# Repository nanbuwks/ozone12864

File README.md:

# OZONE12864

ESP32 ozone meater with LCD JLX12864G-332-BN

# sensor

SPEC electrochemical 3SP_O3_20 DIP 

# principle

Potentiostat method. see:
https://qiita.com/nanbuwks/items/b0f3cb8982ab1c29c718

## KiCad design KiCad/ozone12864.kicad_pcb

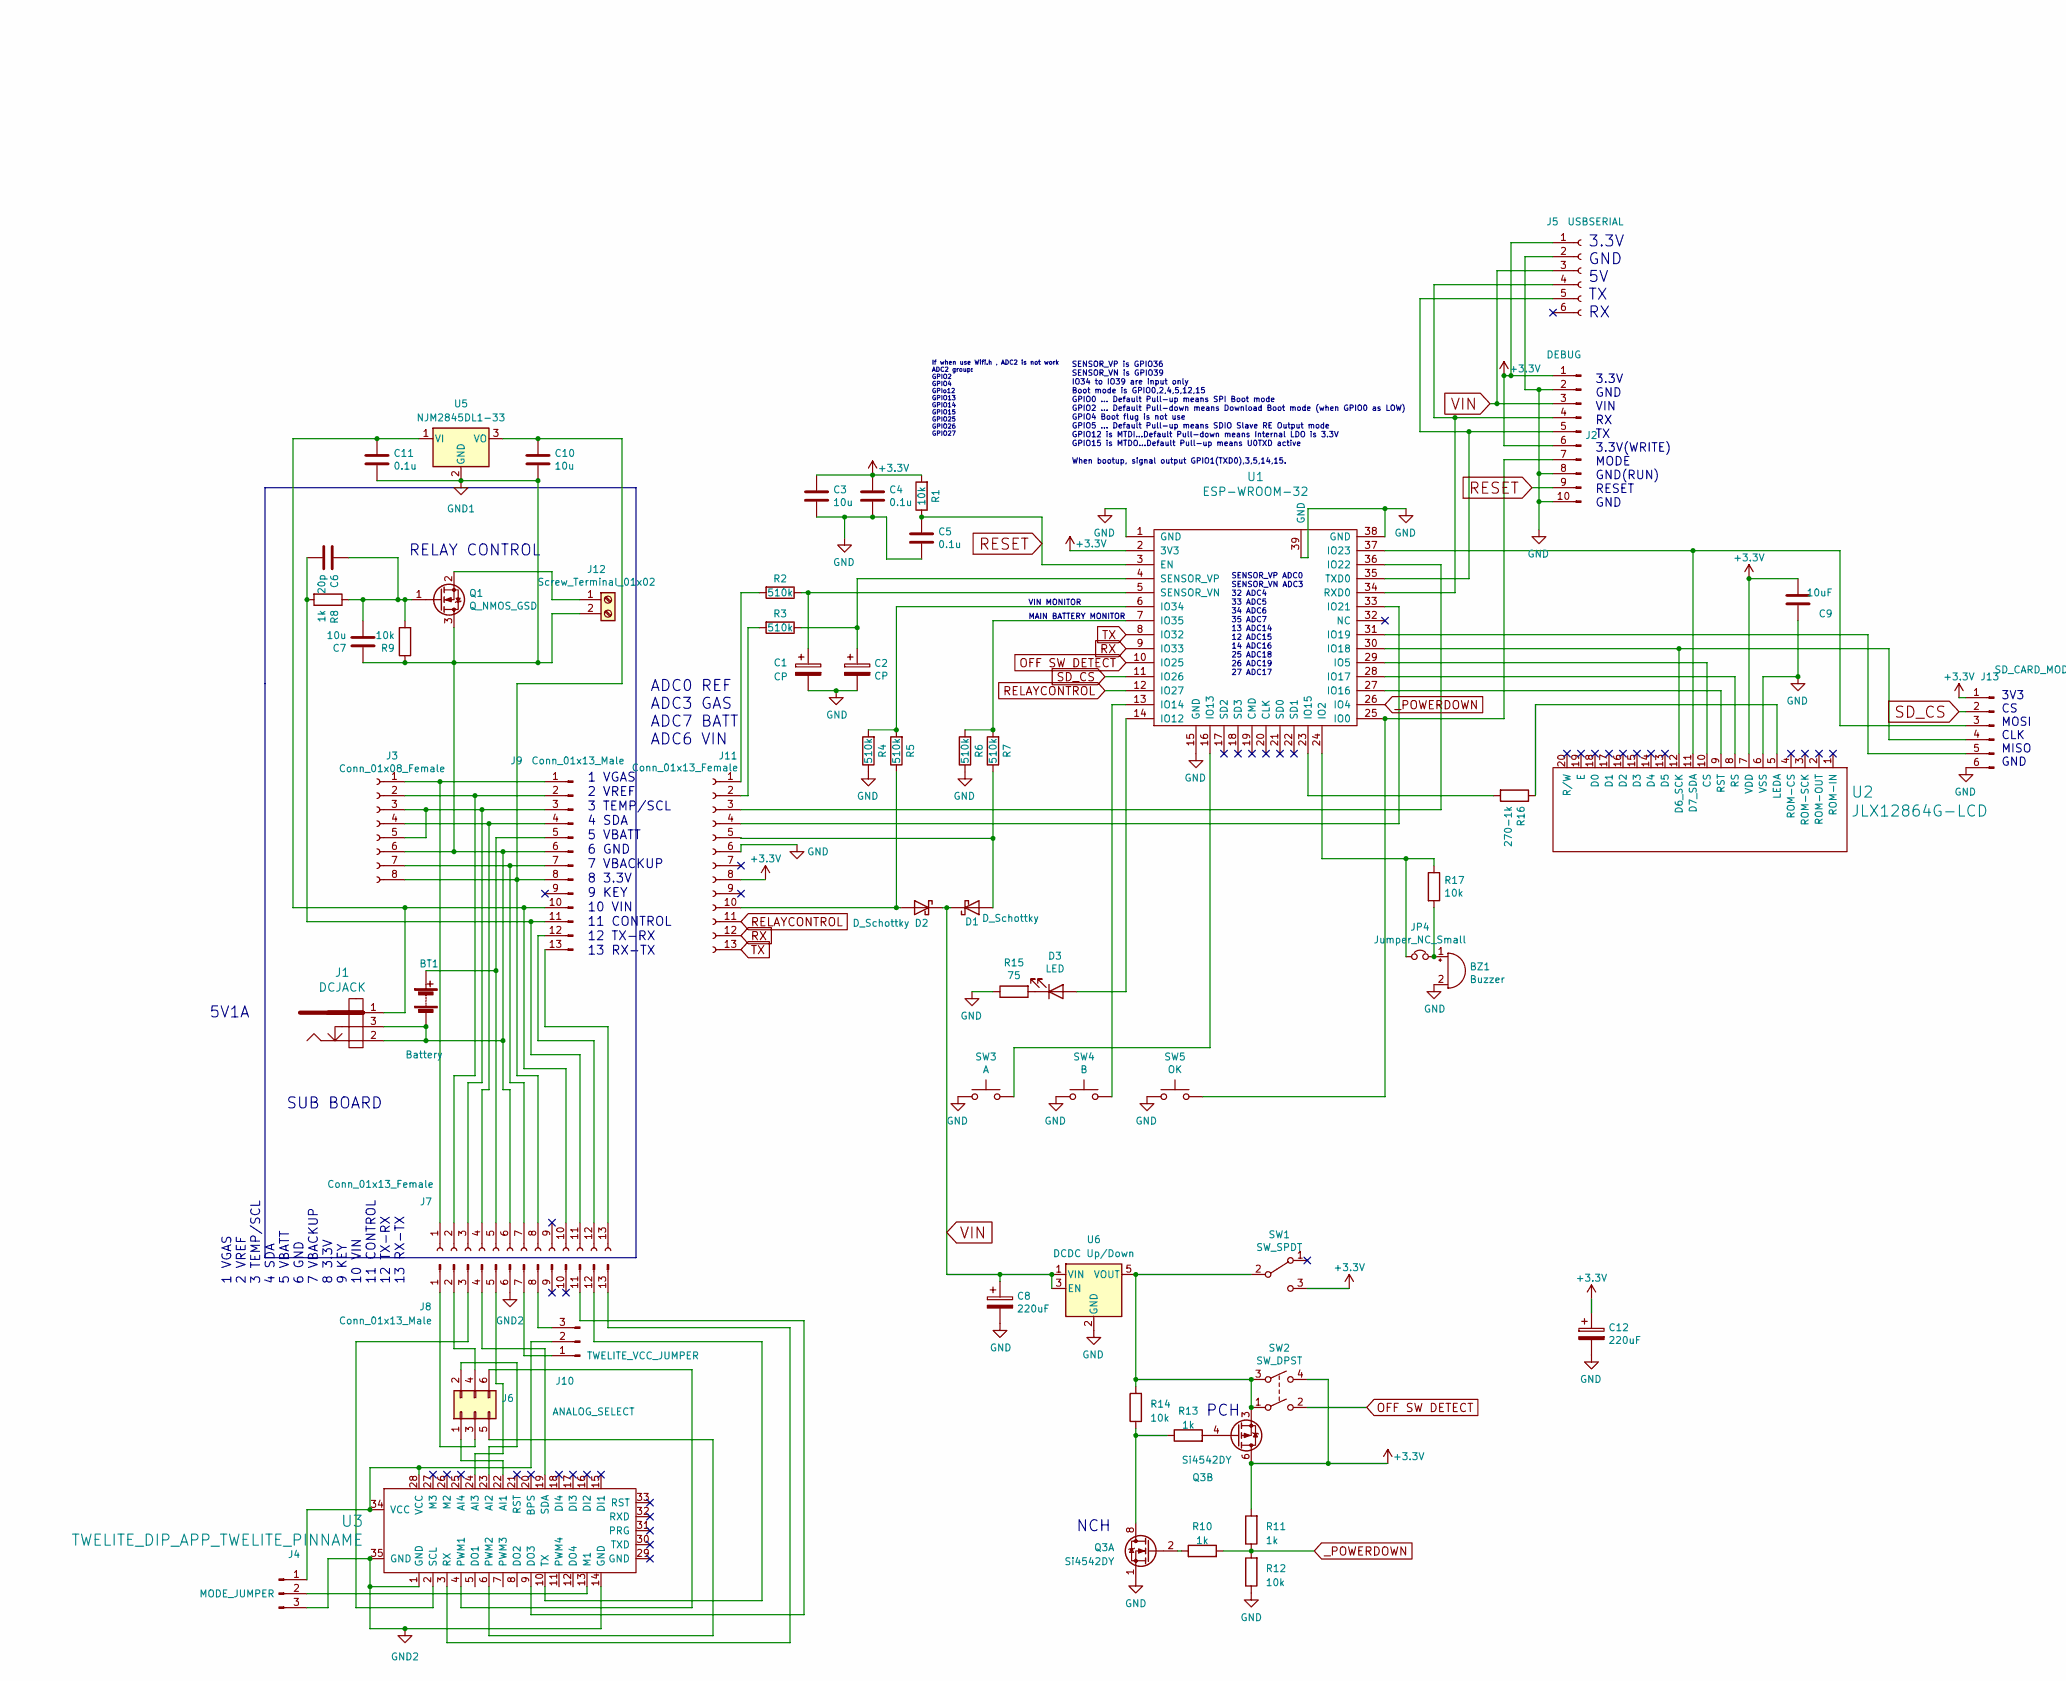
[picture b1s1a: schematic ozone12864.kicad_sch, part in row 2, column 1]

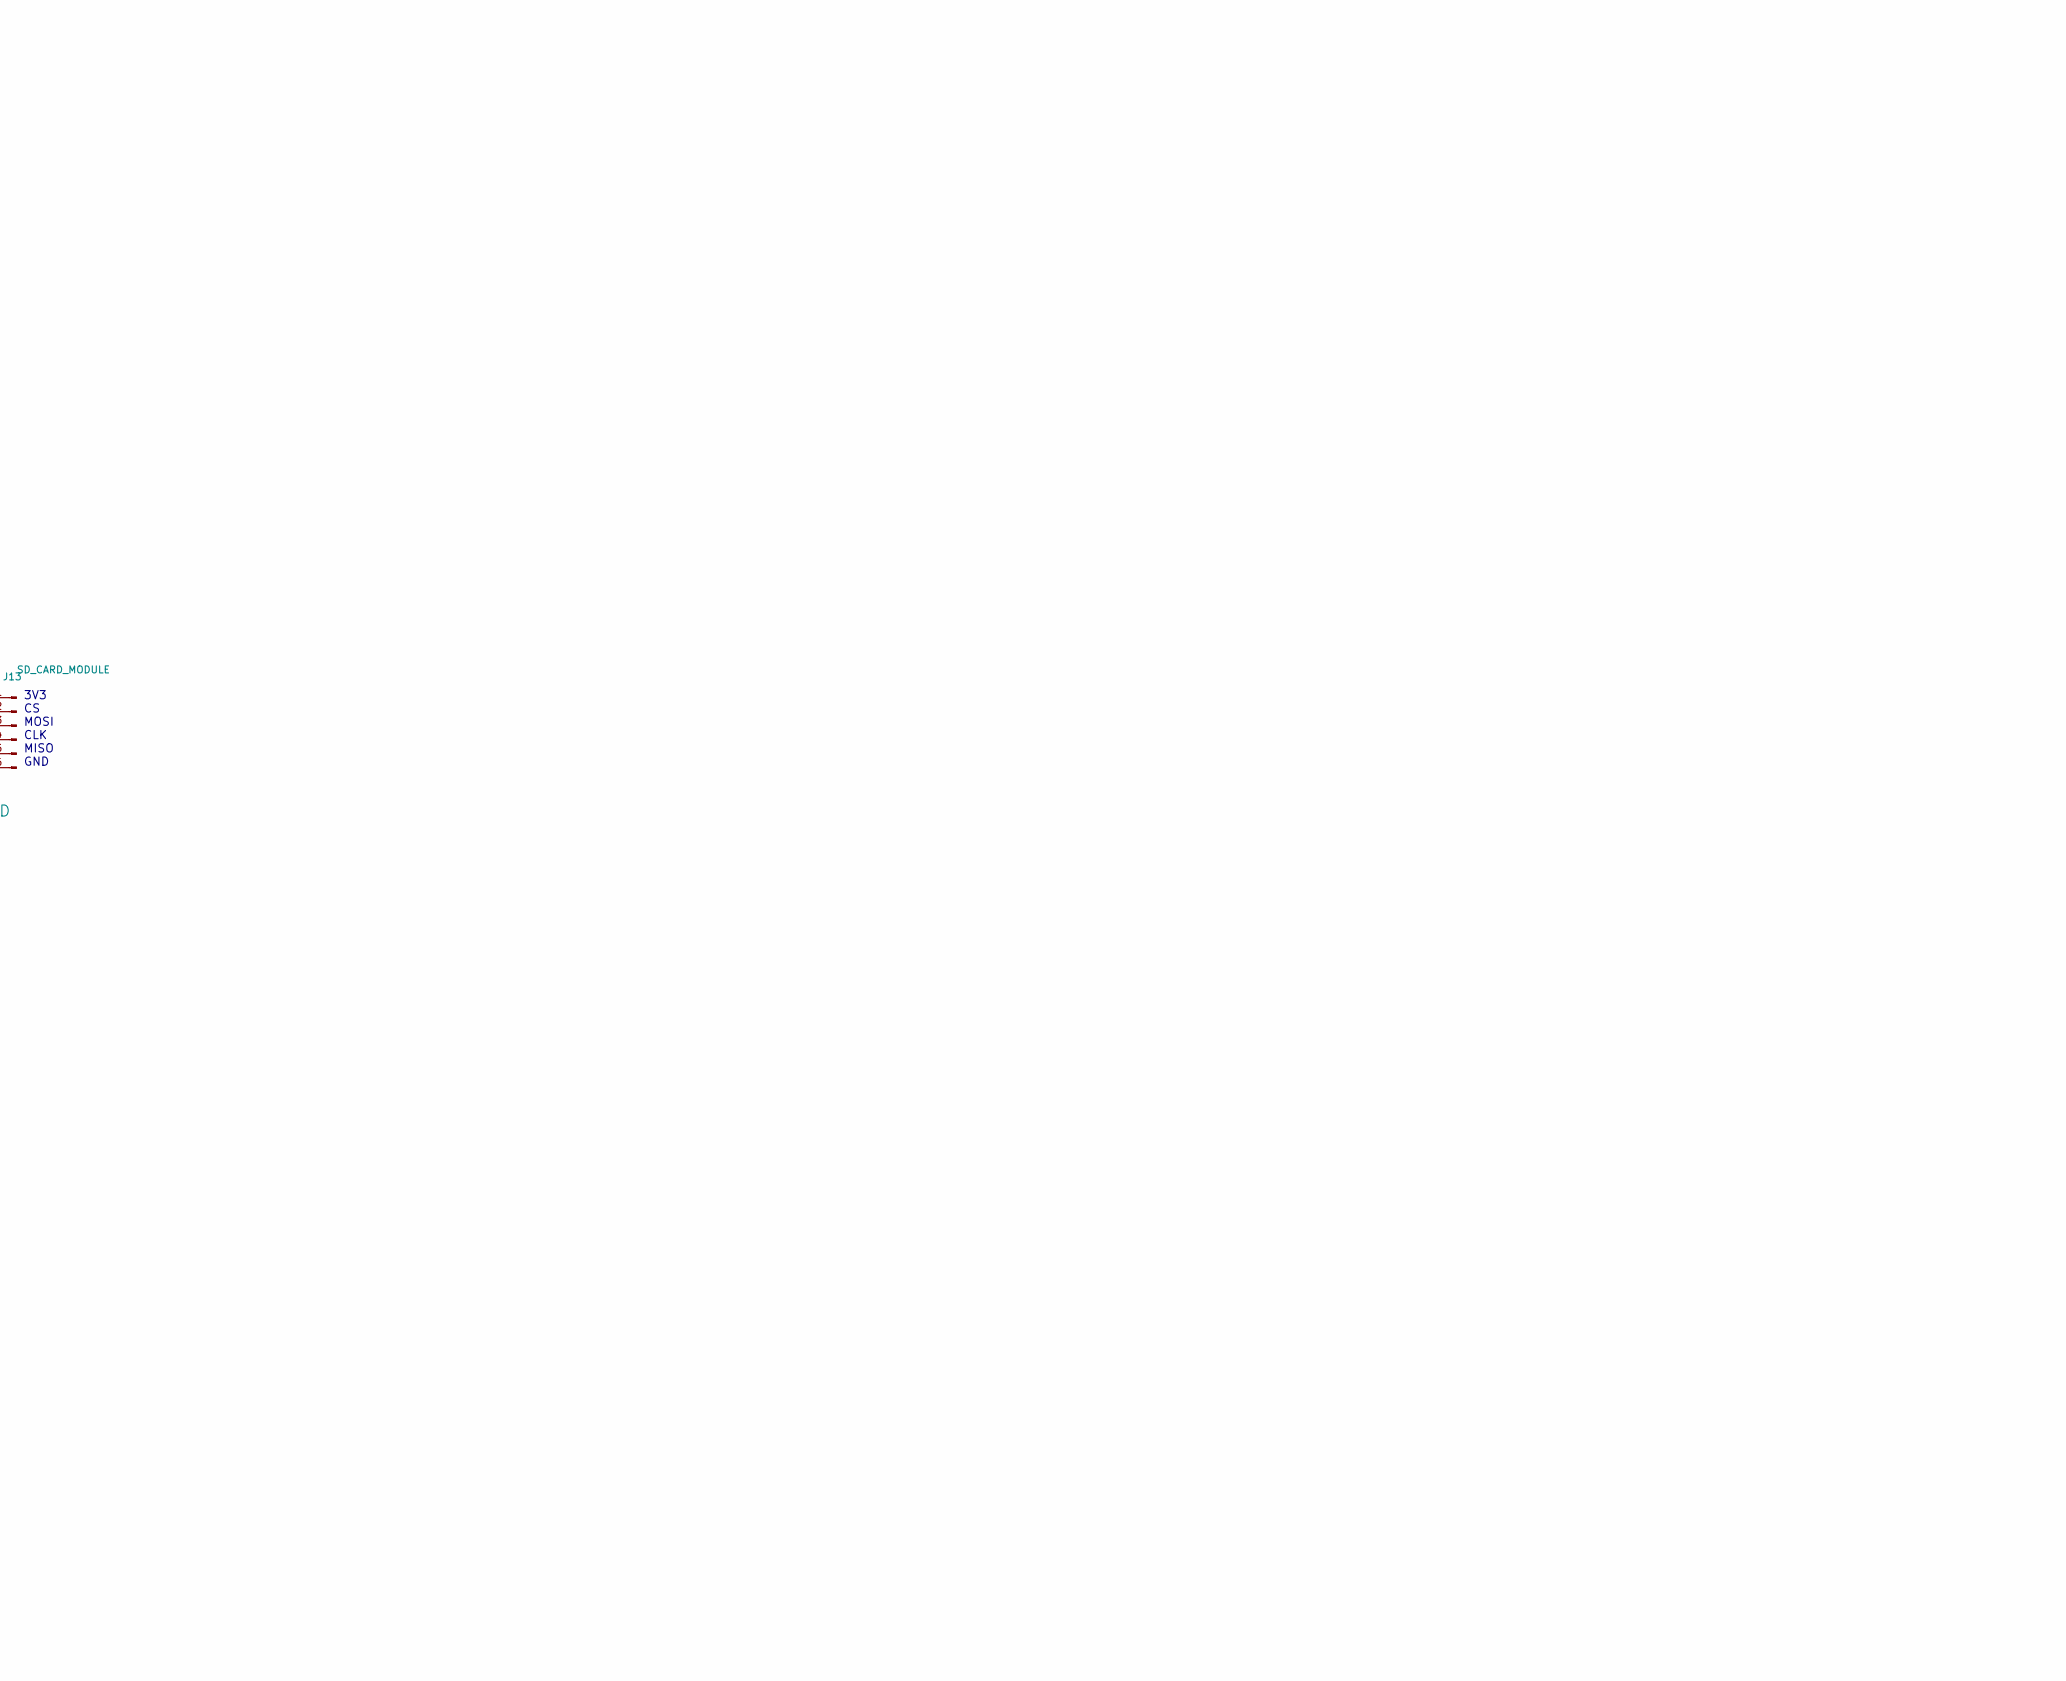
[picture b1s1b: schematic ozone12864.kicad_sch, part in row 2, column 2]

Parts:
BT1: Battery; JST_XH_B2B-XH-AM_1x02_P2.50mm_Vertical
BZ1: Buzzer; MagneticBuzzer_ProSignal_ABI-010-RC
C1, C2: CP; CP_Radial_D5.0mm_P2.00mm
C3, C7, C10: 10u; C_0603_1608Metric
C4, C5, C11: 0.1u; C_0603_1608Metric
C6: 20p; C_0603_1608Metric
C8, C12: 220uF; CP_Radial_D5.0mm_P2.00mm
C9: 10uF; C_0603_1608Metric
D1, D2: D_Schottky; D_SOD-123
D3: LED; LED_D3.0mm
J1: DCJACK
J2: DEBUG; PinHeader_1x10_P2.54mm_Vertical
J3: Conn_01x08_Female; PinHeader_1x08_P2.54mm_Vertical
J4: MODE_JUMPER; PinHeader_1x03_P2.54mm_Vertical
J5: USBSERIAL; PinSocket_1x06_P2.54mm_Horizontal
J6: ANALOG_SELECT; PinHeader_2x03_P2.54mm_Vertical
J7, J11: Conn_01x13_Female; PinHeader_1x13_P2.54mm_Vertical
J8: Conn_01x13_Male; PinHeader_1x13_P2.54mm_Vertical
J9: Conn_01x13_Male; PinSocket_1x13_P2.54mm_Horizontal
J10: TWELITE_VCC_JUMPER; PinHeader_1x03_P2.54mm_Vertical
J12: Screw_Terminal_01x02; TerminalBlock_Phoenix_MKDS-1,5-2-5.08_1x02_P5.08mm_Horizont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
J13: SD_CARD_MODULE; PinHeader_1x06_P2.54mm_Vertical
JP4: Jumper_NC_Small; SolderJumper-2_P1.3mm_Bridged_RoundedPad1.0x1.5mm
Q1: Q_NMOS_GSD; TO-252-2
Q3: Si4542DY; SO-8_5.3x6.2mm_P1.27mm
R1, R9, R12, R14, R17: 10k; R_0603_1608Metric
R2, R3, R4, R5, R6, R7: 510k; R_0603_1608Metric
R8, R10, R11, R13: 1k; R_0603_1608Metric
R15: 75; R_0603_1608Metric
R16: 270-1k; R_0603_1608Metric
SW1: SW_SPDT; SS-12F23_SLIDE_SWITCH
SW2: SW_DPST; 5.8x5.8_7.0x7.0_8.5x8.5_SWITCH_EDGEMOUNT
SW3: A; SW_PUSH_6mm
SW4: B; SW_PUSH_6mm
SW5: OK; SW_PUSH_6mm
U1: ESP-WROOM-32
U2: JLX12864G-LCD; JLX12864G_128x64_2.11in_LCD_Module
U3: TWELITE_DIP_APP_TWELITE_PINNAME; TWE-LITE-DIP-PCB
U5: NJM2845DL1-33; TO-252-2
U6: DCDC Up/Down; TPS63020_Module_Both_Strawberrylinux_Taobao

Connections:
+3V3: C3.1, C4.1, C9.2, C12.1, J2.1, J2.6, J5.1, J11.8, J13.1, Q3.5 (D), Q3.6 (D), R1.2, R11.2, SW1.3 (C), SW2.4, U1.2 (3V3), U2.7 (VDD)
GND: BZ1.2 (+), C1.2, C2.2, C3.2, C4.2, C5.2, C8.2, C9.1, C12.2, J2.2, J2.8, J2.10, J5.2, J11.6, J13.6, Q3.1 (S), R4.1, R6.1, R12.1, R15.1, SW3.1, SW4.1, SW5.1, U1.1 (GND), U1.15 (GND), U1.38 (GND), U1.39 (GND), U2.6 (VSS), U6.2 (GND)
GND1: BT1.2 (-), C7.1, C10.2, C11.2, J1.2, J1.3, J3.6, J7.6, J9.6, J12.2, Q1.3 (D), R9.1, U5.2 (GND)
unnamed: BT1.1 (+), J7.5, J9.5
unnamed: BZ1.1 (-), JP4.2, R17.2
unnamed: D1.2 (A), J11.5, R7.1
unnamed: D2.2 (A), J11.10, R5.1
unnamed: D3.2 (A), U1.14 (IO12)
unnamed: D3.1 (K), R15.2
unnamed: J2.4, J5.4, U1.34 (RXD0)
unnamed: J2.5, J5.5, U1.35 (TXD0)
unnamed: J2.7, SW5.2, U1.25 (IO0)
unnamed: J3.1, J7.1, J9.1
unnamed: J3.2, J7.2, J9.2
unnamed: J3.3, J3.5, J7.3, J9.3
unnamed: J3.4, J7.4, J9.4
unnamed: J3.7, J7.7, J9.7
unnamed: C10.1, J3.8, J7.8, J9.8, U5.3 (VO)
unnamed: J4.2, U3.13 (M1)
unnamed: J4.3, J8.6, U3.1 (GND), U3.14 (GND), U3.35 (GND)
unnamed: J6.1, U3.22 (AI1)
unnamed: J6.2, U3.23 (AI2)
unnamed: J6.3, J8.1
unnamed: J6.4, J8.2
unnamed: J6.5, U3.6 (PWM2)
unnamed: J6.6, U3.4 (PWM1)
unnamed: C11.1, J1.1, J7.10, J9.10, U5.1 (VI)
unnamed: C6.2, J7.11, J9.11, R8.2
unnamed: J7.12, J9.12
unnamed: J7.13, J9.13
unnamed: J8.3, U3.2 (SCL)
unnamed: J8.4, U3.19 (SDA)
unnamed: J8.5, U3.24 (AI3)
unnamed: J8.11, U3.9 (DO3)
unnamed: J8.12, U3.10 (TX)
unnamed: J8.13, U3.3 (RX)
unnamed: J8.7, J10.1
unnamed: J4.1, J10.2, U3.28 (VCC), U3.34 (VCC)
unnamed: J8.8, J10.3
unnamed: J11.1, R2.2
unnamed: J11.2, R3.2
unnamed: J11.3, U1.36 (IO22)
unnamed: J11.4, U1.33 (IO21)
unnamed: J12.1, Q1.2 (S)
unnamed: J13.3, U1.37 (IO23), U2.11 (D7_SDA)
unnamed: J13.4, U1.30 (IO18), U2.12 (D6_SCK)
unnamed: J13.5, U1.31 (IO19)
unnamed: C6.1, C7.2, Q1.1 (G), R8.1, R9.2
unnamed: Q3.7 (D), Q3.8 (D), R13.1, R14.1
unnamed: Q3.2 (G), R10.1
unnamed: Q3.3 (1), R14.2, SW1.2 (B), SW2.1, SW2.3, U6.5 (VOUT)
unnamed: Q3.4 (G), R13.2
unnamed: JP4.1, R17.1, U1.24 (IO2)
unnamed: U1.29 (IO5), U2.10 (CS)
unnamed: SW3.2, U1.16 (IO13)
unnamed: SW4.2, U1.13 (IO14)
unnamed: R16.2, U1.23 (IO15)
unnamed: U1.27 (IO16), U2.9 (RST)
unnamed: U1.28 (IO17), U2.8 (RS)
unnamed: R4.2, R5.2, U1.6 (IO34)
unnamed: R6.2, R7.2, U1.7 (IO35)
unnamed: C1.1, R2.1, U1.5 (SENSOR_VN)
unnamed: C2.1, R3.1, U1.4 (SENSOR_VP)
unnamed: R16.1, U2.5 (LEDA)
OFF SW DETECT: SW2.2, U1.10 (IO25)
RELAYCONTROL: J11.11, U1.12 (IO27)
RESET: C5.1, J2.9, R1.1, U1.3 (EN)
RX: J11.12, U1.9 (IO33)
SD_CS: J13.2, U1.11 (IO26)
TX: J11.13, U1.8 (IO32)
VIN: C8.1, D1.1 (K), D2.1 (K), J2.3, J5.3, U6.1 (VIN), U6.3 (EN)
_POWERDOWN: R10.2, R11.1, R12.2, U1.26 (IO4)

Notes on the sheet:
ADC0 REF ADC3 GAS ADC7 BATT ADC6 VIN
3.3V GND VIN RX TX 3.3V(WRITE) MODE GND(RUN) RESET GND
PCH
If when use Wifi.h , ADC2 is not work ADC2 group: GPIO2 GPIO4 GPIo12 GPIO13 GPIO14 GPIO15 GPIO25 GPIO26 GPIO27
SUB BOARD
SENSOR_VP is GPIO36 SENSOR_VN is GPIO39 IO34 to IO39 are input only Boot mode is GPIO0,2,4,5,12,15 GPIO0 ... Default Pull-up means SPI Boot mode GPIO2 ... Default Pull-down means Download Boot mode (when GPIO0 as LOW) GPIO4 Boot flug is not use GPIO5 ... Default Pull-up means SDIO Slave RE Output m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
RELAY CONTROL
3.3V GND 5V TX RX
MAIN BATTERY MONITOR
1 VGAS 2 VREF 3 TEMP/SCL 4 SDA 5 VBATT 6 GND 7 VBACKUP 8 3.3V 9 KEY 10 VIN 11 CONTROL 12 TX-RX 13 RX-TX
VIN MONITOR
NCH
5V1A
SENSOR_VP ADC0 SENSOR_VN ADC3 32 ADC4 33 ADC5 34 ADC6 35 ADC7 13 ADC14 12 ADC15 14 ADC16 25 ADC18 26 ADC19 27 ADC17
3V3 CS MOSI CLK MISO GND

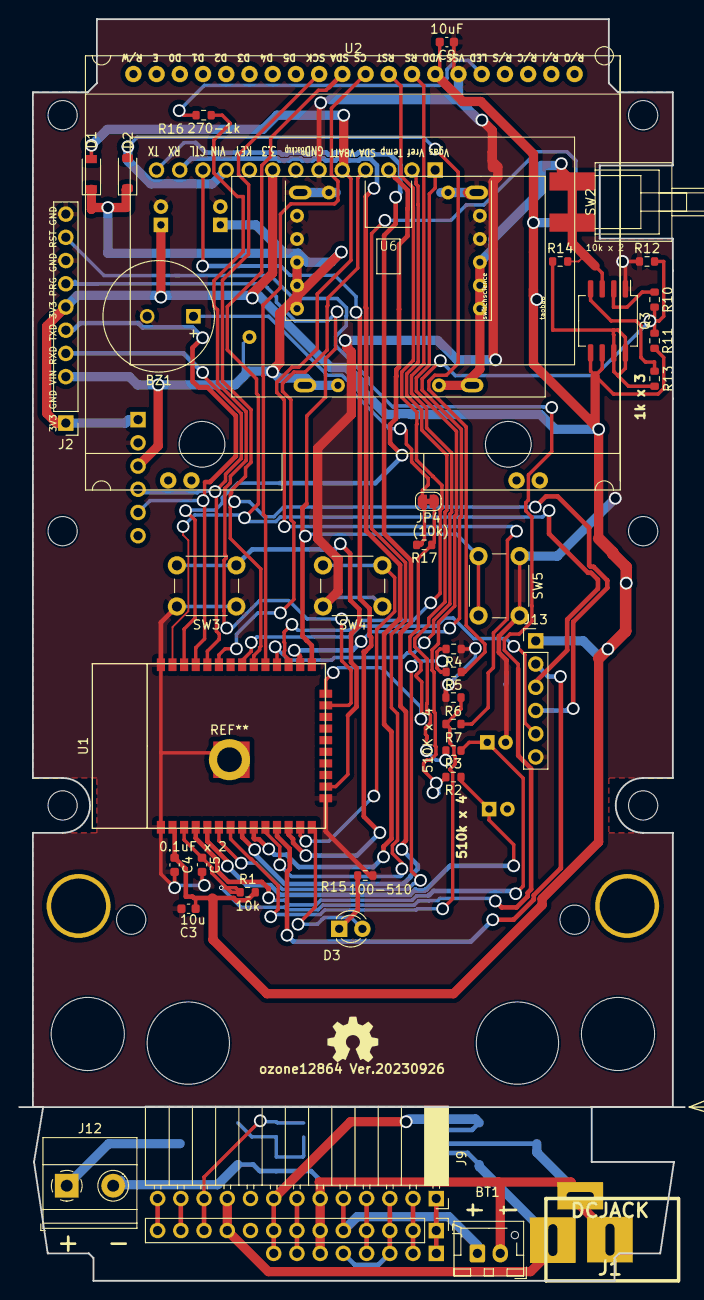
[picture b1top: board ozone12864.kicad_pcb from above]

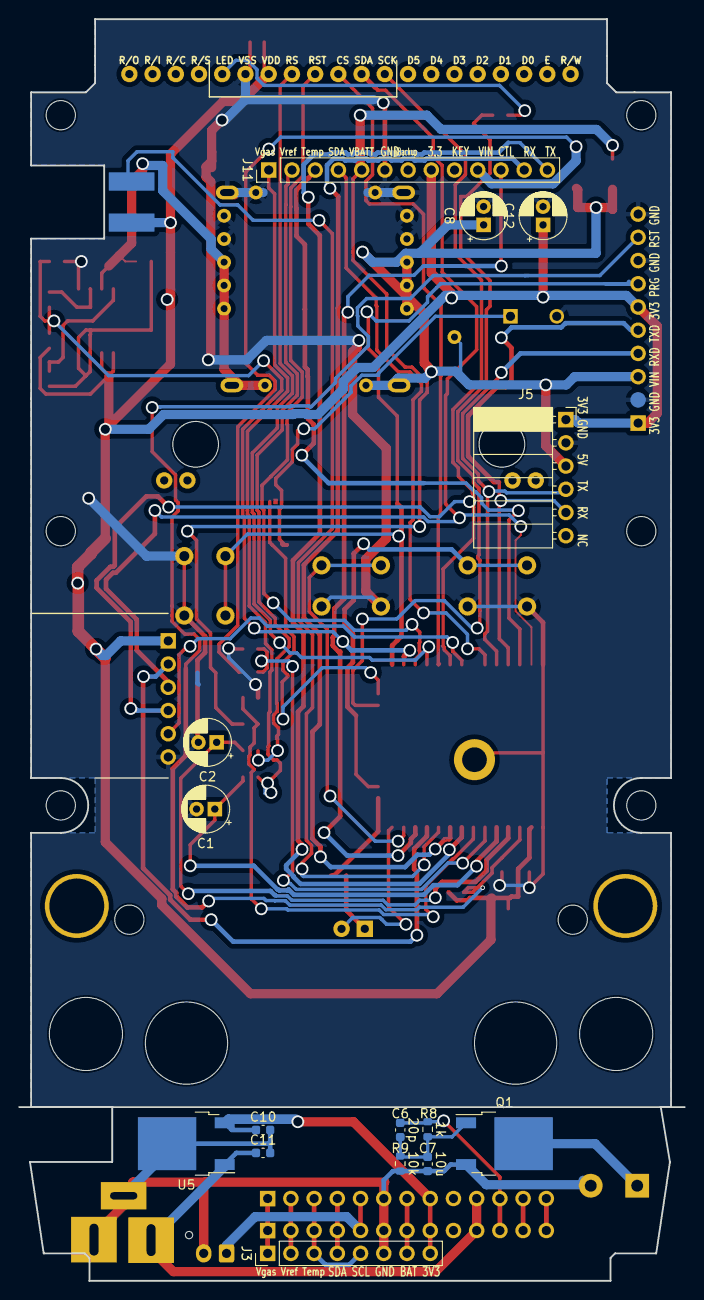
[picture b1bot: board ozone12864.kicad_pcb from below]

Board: 2 copper layers, 72.8 x 138.0 mm, 55 parts (15 on the bottom side), 55 nets.

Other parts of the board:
OSHW: 1.1; OSHW_LOGL_SYLK_5mm

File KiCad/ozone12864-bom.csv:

"ID";"指定子";"フットプリント";"数量";"名称";"供給業者、参考資料";
1;"REF**,REF**";"SolderWirePad_single_1-2mmDrill";2;"SolderWirePad_single_1-2mmDrill";;;
2;"C3,C7,C10";"C_0603_1608Metric";3;"10u";;;
3;"C4,C5,C11";"C_0603_1608Metric";3;"0.1u";;;
4;"D1,D2";"D_SOD-123";2;"D_Schottky";;;
5;"D3";"LED_D3.0mm";1;"LED";;;
6;"J2";"PinHeader_1x10_P2.54mm_Vertical";1;"DEBUG";;;
7;"JP4";"SolderJumper-2_P1.3mm_Bridged_RoundedPad1.0x1.5mm";1;"Jumper_NC_Small";;;
8;"R2,R3,R7,R6,R5,R4";"R_0603_1608Metric";6;"510k";;;
9;"R1,R17,R12,R14,R9";"R_0603_1608Metric";5;"10k";;;
10;"R15";"R_0603_1608Metric";1;"75";;;
11;"U2";"JLX12864G_128x64_2.11in_LCD_Module";1;"JLX12864G-LCD";;;
12;"U1";"ESP-WROOM-32";1;"ESP-WROOM-32";;;
13;"BZ1";"MagneticBuzzer_ProSignal_ABI-010-RC";1;"Buzzer";;;
14;"BT1";"JST_XH_B2B-XH-AM_1x02_P2.50mm_Vertical";1;"Battery";;;
15;"SW2";"5.8x5.8_7.0x7.0_8.5x8.5_SWITCH_EDGEMOUNT";1;"SW_DPST";;;
16;"J13";"PinHeader_1x06_P2.54mm_Vertical";1;"SD_CARD_MODULE";;;
17;"J7,J11";"PinHeader_1x13_P2.54mm_Vertical";2;"Conn_01x13_Female";;;
18;"J12";"TerminalBlock_Phoenix_MKDS-1,5-2-5.08_1x02_P5.08mm_Horizontal";1;"Screw_Terminal_01x02";;;
19;"J9";"PinSocket_1x13_P2.54mm_Horizontal";1;"Conn_01x13_Male";;;
20;"R16";"R_0603_1608Metric";1;"270-1k";;;
21;"C9";"C_0603_1608Metric";1;"10uF";;;
22;"SW4";"SW_PUSH_6mm";1;"B";;;
23;"SW5";"SW_PUSH_6mm";1;"OK";;;
24;"SW3";"SW_PUSH_6mm";1;"A";;;
25;"J1";"DCJACK";1;"DCJACK";;;
26;"OSHW";"OSHW_LOGL_SYLK_5mm";1;"1.1";;;
27;"U6";"TPS63020_Module_Both_Strawberrylinux_Taobao";1;"DCDC Up/Down";;;
28;"R11,R13,R10,R8";"R_0603_1608Metric";4;"1k";;;
29;"Q3";"SO-8_5.3x6.2mm_P1.27mm";1;"Si4542DY";;;
30;"C1,C2";"CP_Radial_D5.0mm_P2.00mm";2;"CP";;;
31;"J3";"PinHeader_1x08_P2.54mm_Vertical";1;"Conn_01x08_Female";;;
32;"Q1";"TO-252-2";1;"Q_NMOS_GSD";;;
33;"C6";"C_0603_1608Metric";1;"20p";;;
34;"C8,C12";"CP_Radial_D5.0mm_P2.00mm";2;"220uF";;;
35;"J5";"PinSocket_1x06_P2.54mm_Horizontal";1;"USBSERIAL";;;
36;"U5";"TO-252-2";1;"NJM2845DL1-33";;;

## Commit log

2023-07-29 update to ver.202307 version
2023-07-29 update schematic
2023-08-25 fix pcb bug / add arduino sketch
2023-09-26 bug fix
2023-09-26 PCB pattern bug fix
2024-02-08 LovyanGFX test
2024-02-08 update arduino sketch
2024-02-16 update 0.5 ppm control
2024-02-22 add paramater save in arduino sketch
2024-02-22 make menu arduino sketch
2024-08-29 arduino sketch update for value display at web browser
2024-09-03 WiFi connect process in asynchronously
2024-09-04 add network setting view to menu
